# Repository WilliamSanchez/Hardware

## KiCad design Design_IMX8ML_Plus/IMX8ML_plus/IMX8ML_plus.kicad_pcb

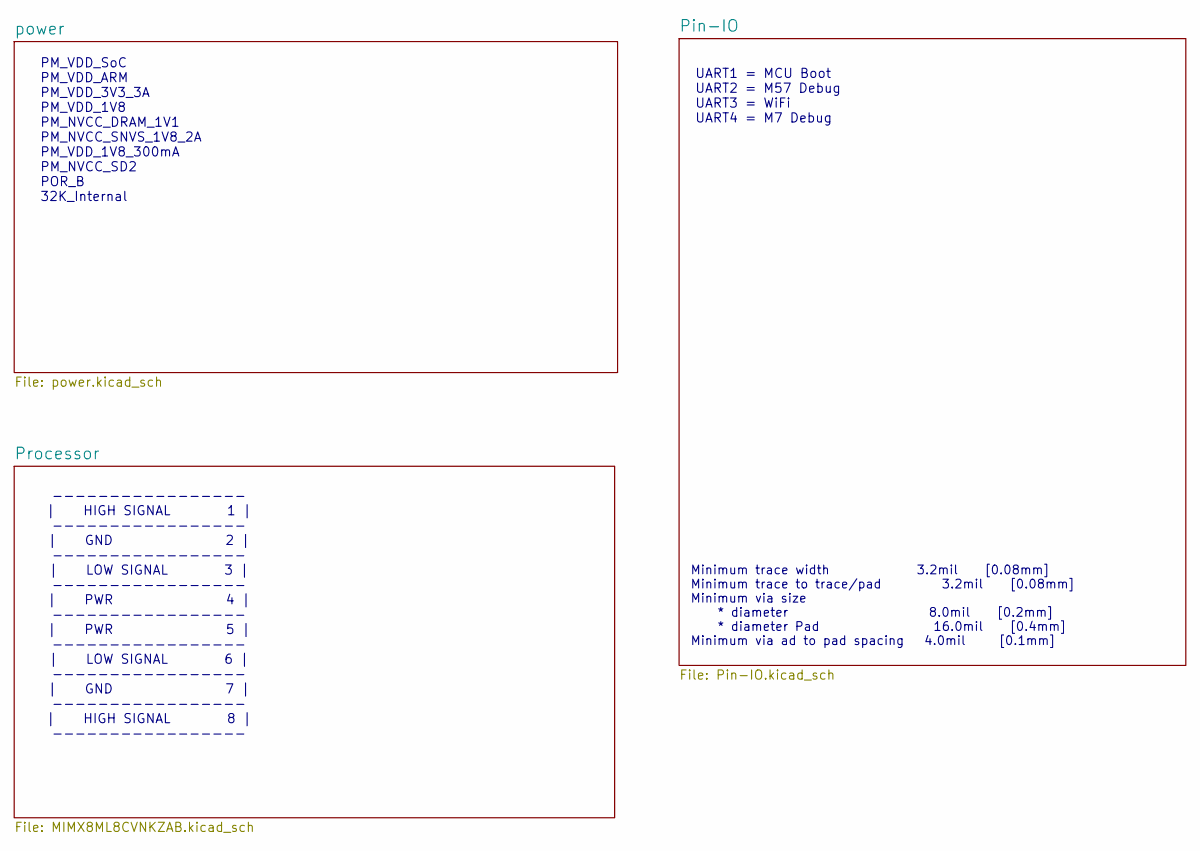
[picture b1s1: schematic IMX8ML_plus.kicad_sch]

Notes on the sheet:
----------------- | HIGH SIGNAL 1 | ----------------- | GND 2 | ----------------- | LOW SIGNAL 3 | ----------------- | PWR 4 | ----------------- | PWR 5 | ----------------- | LOW SIGNAL 6 | ----------------- | GND 7 | ----------------- | HIGH SIGNAL 8 | -----------------
UART1 = MCU Boot UART2 = M57 Debug UART3 = WiFi UART4 = M7 Debug
Minimum trace width 3.2mil [0.08mm] Minimum trace to trace/pad 3.2mil [0.08mm] Minimum via size * diameter 8.0mil [0.2mm] * diameter Pad 16.0mil [0.4mm] Minimum via ad to pad spacing 4.0mil [0.1mm]
PM_VDD_SoC PM_VDD_ARM PM_VDD_3V3_3A PM_VDD_1V8 PM_NVCC_DRAM_1V1 PM_NVCC_SNVS_1V8_2A PM_VDD_1V8_300mA PM_NVCC_SD2 POR_B 32K_Internal

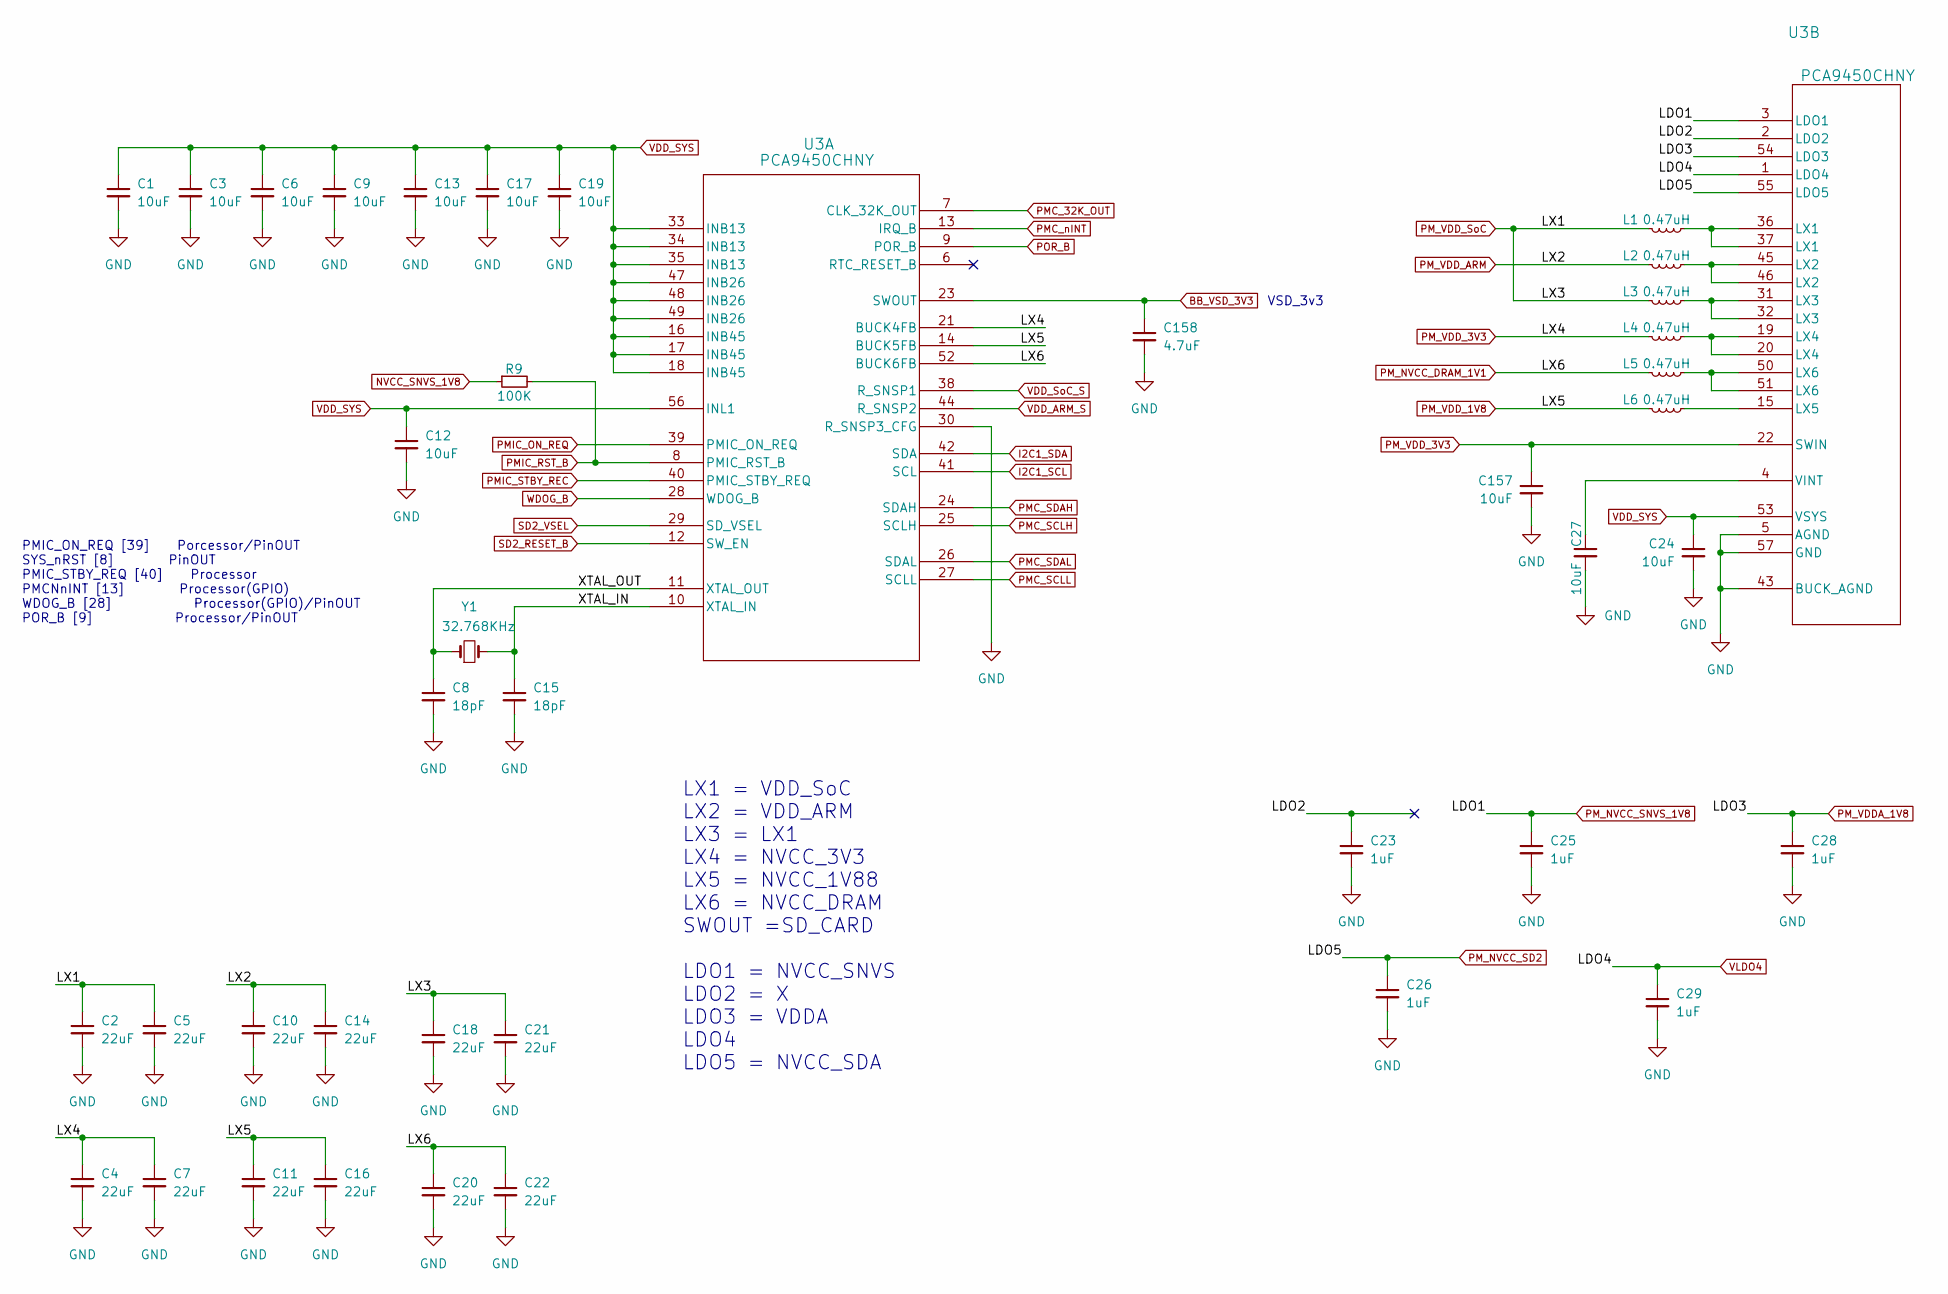
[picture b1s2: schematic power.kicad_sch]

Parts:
C1, C3, C6, C9, C12, C13, C17, C19, C157: 10uF; C_0603_1608Metric
C2, C4, C5, C7, C10, C11, C14, C16, C18, C20, C21, C22: 22uF; C_0603_1608Metric
C8, C15: 18pF; C_0201_0603Metric
C23, C25, C26, C28, C29: 1uF; C_0201_0603Metric
C24, C27: 10uF; C_0402_1005Metric
C158: 4.7uF; C_0402_1005Metric
L1, L2, L3, L4: 0.47uH; L_APV_ANR252012
L5, L6: 0.47uH; L_Cenker_CKCS201610
R9: 100K; R_0402_1005Metric
U3: PCA9450CHNY; HVQFN56_SOT949-6_NXP
Y1: 32.768KHz; Crystal_SMD_3215-2Pin_3.2x1.5mm

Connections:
/power/LDO2: C23.1, U3.2 (LDO2)
/power/XTAL_IN: C15.1, U3.10 (XTAL_IN), Y1.2
/power/XTAL_OUT: C8.1, U3.11 (XTAL_OUT), Y1.1
BB_VSD_3V3: C158.1, U3.23 (SWOUT)
GND: C1.2, C2.2, C3.2, C4.2, C5.2, C6.2, C7.2, C8.2, C9.2, C10.2, C11.2, C12.2, C13.2, C14.2, C15.2, C16.2, C17.2, C18.2, C19.2, C20.2, C21.2, C22.2, C23.2, C24.2, C25.2, C26.2, C27.2, C28.2, C29.2, C157.2, C158.2, U3.5 (AGND), U3.30 (R_SNSP3_CFG), U3.43 (BUCK_AGND), U3.57 (GND); also elsewhere on the board
I2C1_SCL: U3.41 (SCL); also elsewhere on the board
I2C1_SDA: U3.42 (SDA); also elsewhere on the board
NVCC_SD2: C26.1, U3.55 (LDO5); also elsewhere on the board
NVCC_SNVS_1V8: C25.1, R9.1, U3.3 (LDO1); also elsewhere on the board
unnamed: L1.1, U3.36 (LX1), U3.37 (LX1)
unnamed: L2.1, U3.45 (LX2), U3.46 (LX2)
unnamed: L3.1, U3.31 (LX3), U3.32 (LX3)
unnamed: L4.1, U3.19 (LX4), U3.20 (LX4)
unnamed: L5.1, U3.50 (LX6), U3.51 (LX6)
unnamed: L6.1, U3.15 (LX5)
unnamed: C27.1, U3.4 (VINT)
PMC_32K_OUT: U3.7 (CLK_32K_OUT)
PMC_SCLH: U3.25 (SCLH)
PMC_SCLL: U3.27 (SCLL)
PMC_SDAH: U3.24 (SDAH)
PMC_SDAL: U3.26 (SDAL)
PMC_nINT: U3.13 (IRQ_B); also elsewhere on the board
PMIC_ON_REQ: U3.39 (PMIC_ON_REQ); also elsewhere on the board
PMIC_RST_B: R9.2, U3.8 (PMIC_RST_B); also elsewhere on the board
PMIC_STBY_REC: U3.40 (PMIC_STBY_REQ); also elsewhere on the board
PM_NVCC_DRAM_1V1: C20.1, C22.1, L5.2, U3.52 (BUCK6FB)
PM_VDDA_1V8: C28.1, U3.54 (LDO3); also elsewhere on the board
PM_VDD_1V8: C11.1, C16.1, L6.2, U3.14 (BUCK5FB)
PM_VDD_3V3: C4.1, C7.1, C157.1, L4.2, U3.21 (BUCK4FB), U3.22 (SWIN); also elsewhere on the board
PM_VDD_ARM: C10.1, C14.1, L2.2, U3.44 (R_SNSP2); also elsewhere on the board
PM_VDD_SoC: C2.1, C5.1, C18.1, C21.1, L1.2, L3.2, U3.38 (R_SNSP1); also elsewhere on the board
POR_B: U3.9 (POR_B); also elsewhere on the board
SD2_RESET_B: U3.12 (SW_EN)
SD2_VSEL: U3.29 (SD_VSEL); also elsewhere on the board
VDD_SYS: C1.1, C3.1, C6.1, C9.1, C12.1, C13.1, C17.1, C19.1, C24.1, U3.16 (INB45), U3.17 (INB45), U3.18 (INB45), U3.33 (INB13), U3.34 (INB13), U3.35 (INB13), U3.47 (INB26), U3.48 (INB26), U3.49 (INB26), U3.53 (VSYS), U3.56 (INL1); also elsewhere on the board
VLDO4: C29.1, U3.1 (LDO4)
WDOG_B: U3.28 (WDOG_B); also elsewhere on the board

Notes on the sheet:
VSD_3v3
LX1 = VDD_SoC LX2 = VDD_ARM LX3 = LX1 LX4 = NVCC_3V3 LX5 = NVCC_1V88 LX6 = NVCC_DRAM SWOUT =SD_CARD LDO1 = NVCC_SNVS LDO2 = X LDO3 = VDDA LDO4 LDO5 = NVCC_SDA
PMIC_ON_REQ [39] Porcessor/PinOUT SYS_nRST [8] PinOUT PMIC_STBY_REQ [40] Processor PMCNnINT [13] Processor(GPIO) WDOG_B [28] Processor(GPIO)/PinOUT POR_B [9] Processor/PinOUT

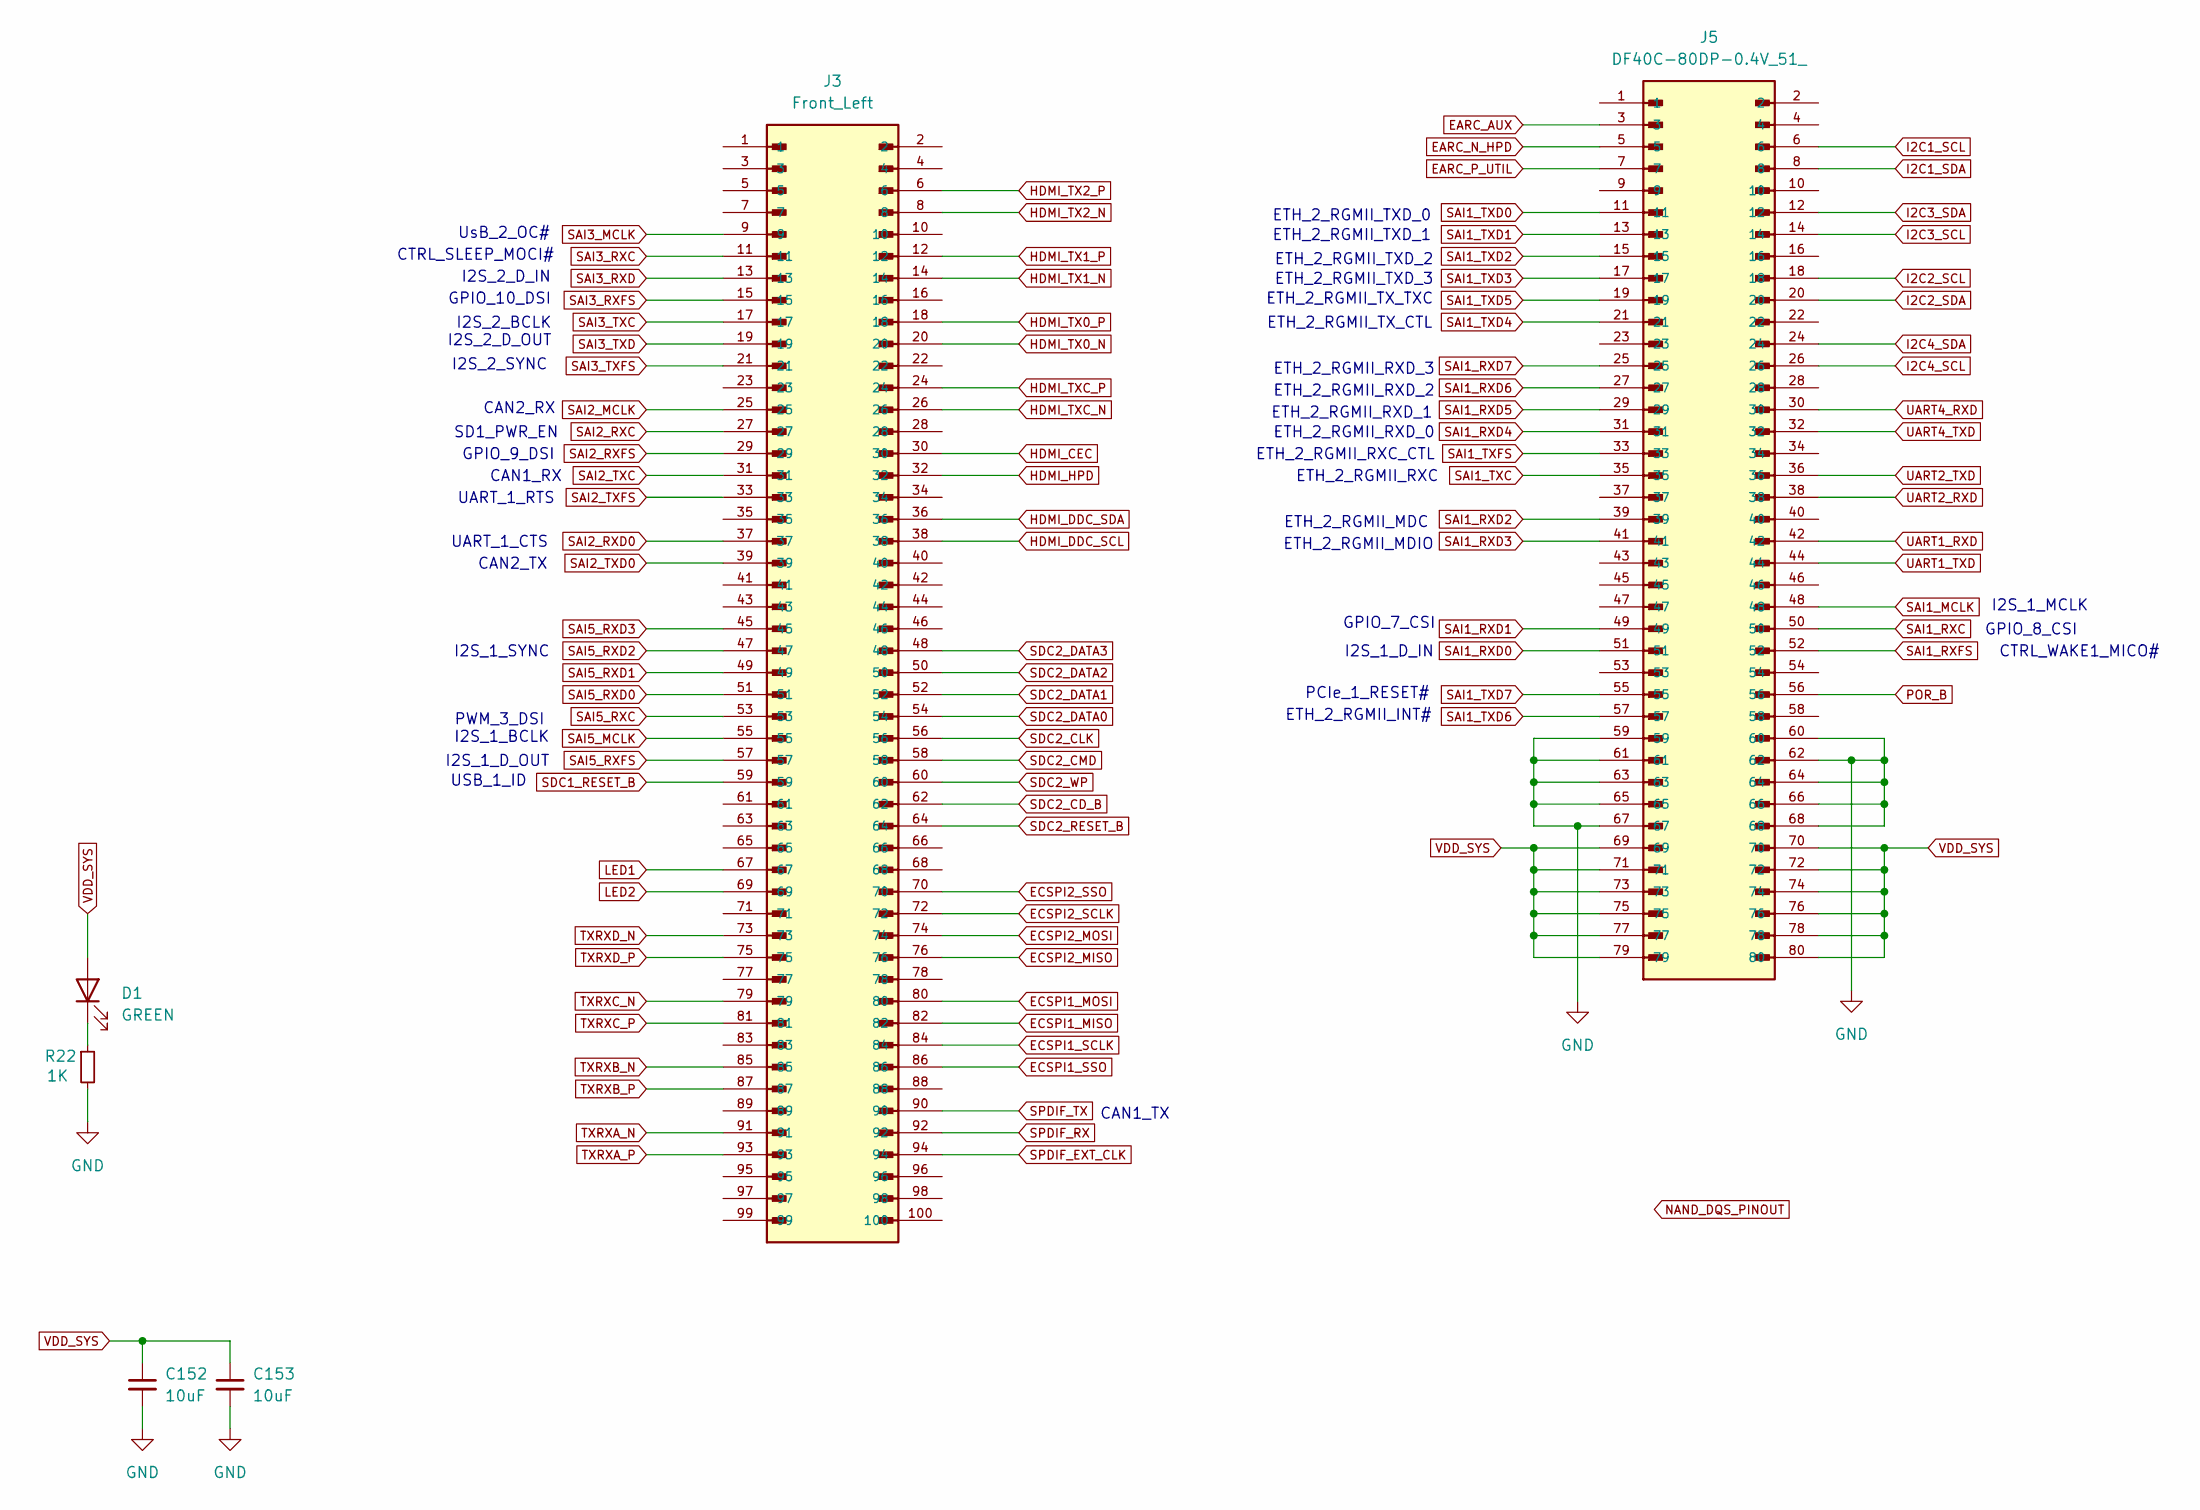
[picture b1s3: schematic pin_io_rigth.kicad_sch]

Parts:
C152, C153: 10uF; C_0603_1608Metric
D1: GREEN; LED_0603_1608Metric
J3: Front_Left; HIROSE_DF40C-100DS-0.4V_51_; PARTREV 8
J5: DF40C-80DP-0.4V_51_; HRS_DF40C-80DS-0.4V_51_
R22: 1K; R_0402_1005Metric

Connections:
EARC_AUX: J5.3; also elsewhere on the board
EARC_N_HPD: J5.5; also elsewhere on the board
EARC_P_UTIL: J5.7; also elsewhere on the board
ECSPI1_MISO: J3.82; also elsewhere on the board
ECSPI1_MOSI: J3.80; also elsewhere on the board
ECSPI1_SCLK: J3.84; also elsewhere on the board
ECSPI1_SSO: J3.86; also elsewhere on the board
ECSPI2_MISO: J3.76; also elsewhere on the board
ECSPI2_MOSI: J3.74; also elsewhere on the board
ECSPI2_SCLK: J3.72; also elsewhere on the board
ECSPI2_SSO: J3.70; also elsewhere on the board
GND: C152.2, C153.2, J5.59, J5.60, J5.61, J5.62, J5.63, J5.64, J5.65, J5.66, J5.67, J5.68, R22.2; also elsewhere on the board
HDMI_CEC: J3.30; also elsewhere on the board
HDMI_DDC_SCL: J3.38; also elsewhere on the board
HDMI_DDC_SDA: J3.36; also elsewhere on the board
HDMI_HPD: J3.32; also elsewhere on the board
HDMI_TX0_N: J3.20; also elsewhere on the board
HDMI_TX0_P: J3.18; also elsewhere on the board
HDMI_TX1_N: J3.14; also elsewhere on the board
HDMI_TX1_P: J3.12; also elsewhere on the board
HDMI_TX2_N: J3.8; also elsewhere on the board
HDMI_TX2_P: J3.6; also elsewhere on the board
HDMI_TXC_N: J3.26; also elsewhere on the board
HDMI_TXC_P: J3.24; also elsewhere on the board
I2C1_SCL: J5.6; also elsewhere on the board
I2C1_SDA: J5.8; also elsewhere on the board
I2C2_SCL: J5.18; also elsewhere on the board
I2C2_SDA: J5.20; also elsewhere on the board
I2C3_SCL: J5.14; also elsewhere on the board
I2C3_SDA: J5.12; also elsewhere on the board
I2C4_SCL: J5.26; also elsewhere on the board
I2C4_SDA: J5.24; also elsewhere on the board
LED1: J3.67; also elsewhere on the board
LED2: J3.69; also elsewhere on the board
unnamed: D1.1 (K), R22.1
POR_B: J5.56; also elsewhere on the board
SAI1_MCLK: J5.48; also elsewhere on the board
SAI1_RXC: J5.50; also elsewhere on the board
SAI1_RXD0: J5.51; also elsewhere on the board
SAI1_RXD1: J5.49; also elsewhere on the board
SAI1_RXD2: J5.39; also elsewhere on the board
SAI1_RXD3: J5.41; also elsewhere on the board
SAI1_RXD4: J5.31; also elsewhere on the board
SAI1_RXD5: J5.29; also elsewhere on the board
SAI1_RXD6: J5.27; also elsewhere on the board
SAI1_RXD7: J5.25; also elsewhere on the board
SAI1_RXFS: J5.52; also elsewhere on the board
SAI1_TXC: J5.35; also elsewhere on the board
SAI1_TXD0: J5.11; also elsewhere on the board
SAI1_TXD1: J5.13; also elsewhere on the board
SAI1_TXD2: J5.15; also elsewhere on the board
SAI1_TXD3: J5.17; also elsewhere on the board
SAI1_TXD4: J5.21; also elsewhere on the board
SAI1_TXD5: J5.19; also elsewhere on the board
SAI1_TXD6: J5.57; also elsewhere on the board
SAI1_TXD7: J5.55; also elsewhere on the board
SAI1_TXFS: J5.33; also elsewhere on the board
SAI2_MCLK: J3.25; also elsewhere on the board
SAI2_RXC: J3.27; also elsewhere on the board
SAI2_RXD0: J3.37; also elsewhere on the board
SAI2_RXFS: J3.29; also elsewhere on the board
SAI2_TXC: J3.31; also elsewhere on the board
SAI2_TXD0: J3.39; also elsewhere on the board
SAI2_TXFS: J3.33; also elsewhere on the board
SAI3_MCLK: J3.9; also elsewhere on the board
SAI3_RXC: J3.11; also elsewhere on the board
SAI3_RXD: J3.13; also elsewhere on the board
SAI3_RXFS: J3.15; also elsewhere on the board
SAI3_TXC: J3.17; also elsewhere on the board
SAI3_TXD: J3.19; also elsewhere on the board
SAI3_TXFS: J3.21; also elsewhere on the board
SAI5_MCLK: J3.55; also elsewhere on the board
SAI5_RXC: J3.53; also elsewhere on the board
SAI5_RXD0: J3.51; also elsewhere on the board
SAI5_RXD1: J3.49; also elsewhere on the board
SAI5_RXD2: J3.47; also elsewhere on the board
SAI5_RXD3: J3.45; also elsewhere on the board
SAI5_RXFS: J3.57; also elsewhere on the board
SDC1_RESET_B: J3.59
SDC2_CD_B: J3.62; also elsewhere on the board
SDC2_CLK: J3.56; also elsewhere on the board
SDC2_CMD: J3.58; also elsewhere on the board
SDC2_DATA0: J3.54; also elsewhere on the board
SDC2_DATA1: J3.52; also elsewhere on the board
SDC2_DATA2: J3.50; also elsewhere on the board
SDC2_DATA3: J3.48; also elsewhere on the board
SDC2_RESET_B: J3.64; also elsewhere on the board
SDC2_WP: J3.60; also elsewhere on the board
SPDIF_EXT_CLK: J3.94; also elsewhere on the board
SPDIF_RX: J3.92; also elsewhere on the board
SPDIF_TX: J3.90; also elsewhere on the board
TXRXA_N: J3.91; also elsewhere on the board
TXRXA_P: J3.93; also elsewhere on the board
TXRXB_N: J3.85; also elsewhere on the board
TXRXB_P: J3.87; also elsewhere on the board
TXRXC_N: J3.79; also elsewhere on the board
TXRXC_P: J3.81; also elsewhere on the board
TXRXD_N: J3.73; also elsewhere on the board
TXRXD_P: J3.75; also elsewhere on the board
UART1_RXD: J5.42; also elsewhere on the board
UART1_TXD: J5.44; also elsewhere on the board
UART2_RXD: J5.38; also elsewhere on the board
UART2_TXD: J5.36; also elsewhere on the board
UART4_RXD: J5.30; also elsewhere on the board
UART4_TXD: J5.32; also elsewhere on the board
VDD_SYS: C152.1, C153.1, D1.2 (A), J5.69, J5.70, J5.71, J5.72, J5.73, J5.74, J5.75, J5.76, J5.77, J5.78, J5.79, J5.80; also elsewhere on the board

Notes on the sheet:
PCIe_1_RESET#
I2S_1_MCLK
ETH_2_RGMII_MDC
CTRL_WAKE1_MICO#
CAN1_RX
I2S_2_BCLK
SD1_PWR_EN
I2S_1_D_IN
GPIO_9_DSI
I2S_1_SYNC
ETH_2_RGMII_RXD_3
UART_1_CTS
I2S_2_D_OUT
ETH_2_RGMII_TXD_2
CAN1_TX
ETH_2_RGMII_RXC_CTL
I2S_2_D_IN
ETH_2_RGMII_TXD_3
UART_1_RTS
ETH_2_RGMII_RXD_2
UsB_2_OC#
ETH_2_RGMII_RXD_0
CAN2_TX
I2S_1_D_OUT
I2S_1_BCLK
GPIO_8_CSI
CAN2_RX
ETH_2_RGMII_RXC
PWM_3_DSI
ETH_2_RGMII_TXD_0
GPIO_7_CSI
ETH_2_RGMII_TX_CTL
I2S_2_SYNC
ETH_2_RGMII_TXD_1
ETH_2_RGMII_INT#
USB_1_ID
CTRL_SLEEP_MOCI#
ETH_2_RGMII_TX_TXC
ETH_2_RGMII_MDIO
GPIO_10_DSI

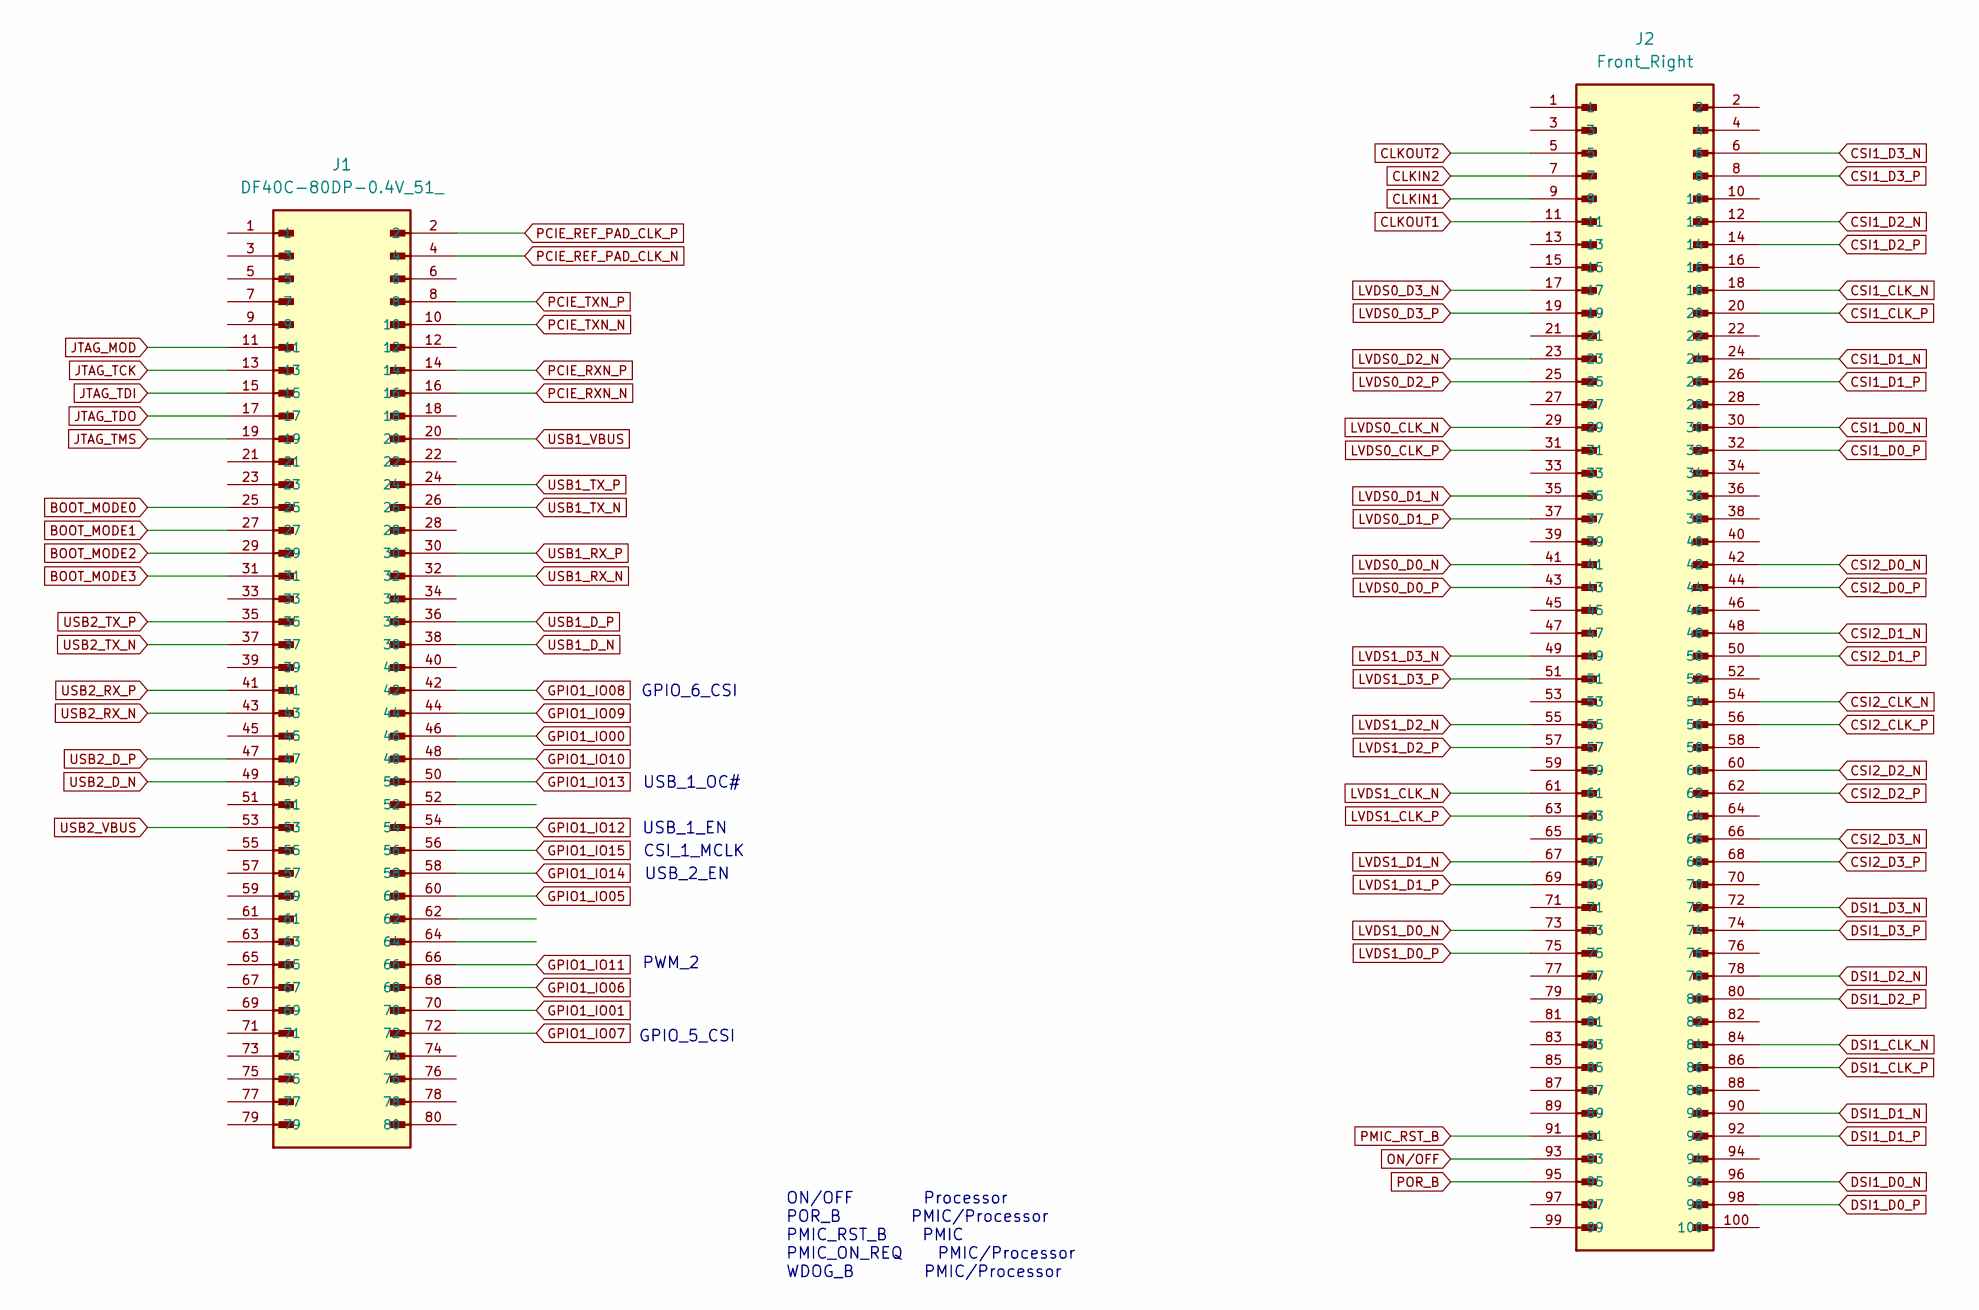
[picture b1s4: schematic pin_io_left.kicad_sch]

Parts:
J1: DF40C-80DP-0.4V_51_; HRS_DF40C-80DS-0.4V_51_
J2: Front_Right; HIROSE_DF40C-100DS-0.4V_51_; PARTREV 8

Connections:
BOOT_MODE0: J1.25; also elsewhere on the board
BOOT_MODE1: J1.27; also elsewhere on the board
BOOT_MODE2: J1.29; also elsewhere on the board
BOOT_MODE3: J1.31; also elsewhere on the board
CLKIN1: J2.9; also elsewhere on the board
CLKIN2: J2.7; also elsewhere on the board
CLKOUT1: J2.11; also elsewhere on the board
CLKOUT2: J2.5; also elsewhere on the board
CSI1_CLK_N: J2.18; also elsewhere on the board
CSI1_CLK_P: J2.20; also elsewhere on the board
CSI1_D0_N: J2.30; also elsewhere on the board
CSI1_D0_P: J2.32; also elsewhere on the board
CSI1_D1_N: J2.24; also elsewhere on the board
CSI1_D1_P: J2.26; also elsewhere on the board
CSI1_D2_N: J2.12; also elsewhere on the board
CSI1_D2_P: J2.14; also elsewhere on the board
CSI1_D3_N: J2.6; also elsewhere on the board
CSI1_D3_P: J2.8; also elsewhere on the board
CSI2_CLK_N: J2.54; also elsewhere on the board
CSI2_CLK_P: J2.56; also elsewhere on the board
CSI2_D0_N: J2.42; also elsewhere on the board
CSI2_D0_P: J2.44; also elsewhere on the board
CSI2_D1_N: J2.48; also elsewhere on the board
CSI2_D1_P: J2.50; also elsewhere on the board
CSI2_D2_N: J2.60; also elsewhere on the board
CSI2_D2_P: J2.62; also elsewhere on the board
CSI2_D3_N: J2.66; also elsewhere on the board
CSI2_D3_P: J2.68; also elsewhere on the board
DSI1_CLK_N: J2.84; also elsewhere on the board
DSI1_CLK_P: J2.86; also elsewhere on the board
DSI1_D0_N: J2.96; also elsewhere on the board
DSI1_D0_P: J2.98; also elsewhere on the board
DSI1_D1_N: J2.90; also elsewhere on the board
DSI1_D1_P: J2.92; also elsewhere on the board
DSI1_D2_N: J2.78; also elsewhere on the board
DSI1_D2_P: J2.80; also elsewhere on the board
DSI1_D3_N: J2.72; also elsewhere on the board
DSI1_D3_P: J2.74; also elsewhere on the board
GPIO1_IO00: J1.46; also elsewhere on the board
GPIO1_IO01: J1.70; also elsewhere on the board
GPIO1_IO05: J1.60; also elsewhere on the board
GPIO1_IO06: J1.68; also elsewhere on the board
GPIO1_IO07: J1.72; also elsewhere on the board
GPIO1_IO08: J1.42; also elsewhere on the board
GPIO1_IO09: J1.44; also elsewhere on the board
GPIO1_IO10: J1.48; also elsewhere on the board
GPIO1_IO11: J1.66; also elsewhere on the board
GPIO1_IO12: J1.54; also elsewhere on the board
GPIO1_IO13: J1.50; also elsewhere on the board
GPIO1_IO14: J1.58; also elsewhere on the board
GPIO1_IO15: J1.56; also elsewhere on the board
JTAG_MOD: J1.11; also elsewhere on the board
JTAG_TCK: J1.13; also elsewhere on the board
JTAG_TDI: J1.15; also elsewhere on the board
JTAG_TDO: J1.17; also elsewhere on the board
JTAG_TMS: J1.19; also elsewhere on the board
LVDS0_CLK_N: J2.29; also elsewhere on the board
LVDS0_CLK_P: J2.31; also elsewhere on the board
LVDS0_D0_N: J2.41; also elsewhere on the board
LVDS0_D0_P: J2.43; also elsewhere on the board
LVDS0_D1_N: J2.35; also elsewhere on the board
LVDS0_D1_P: J2.37; also elsewhere on the board
LVDS0_D2_N: J2.23; also elsewhere on the board
LVDS0_D2_P: J2.25; also elsewhere on the board
LVDS0_D3_N: J2.17; also elsewhere on the board
LVDS0_D3_P: J2.19; also elsewhere on the board
LVDS1_CLK_N: J2.61; also elsewhere on the board
LVDS1_CLK_P: J2.63; also elsewhere on the board
LVDS1_D0_N: J2.73; also elsewhere on the board
LVDS1_D0_P: J2.75; also elsewhere on the board
LVDS1_D1_N: J2.67; also elsewhere on the board
LVDS1_D1_P: J2.69; also elsewhere on the board
LVDS1_D2_N: J2.55; also elsewhere on the board
LVDS1_D2_P: J2.57; also elsewhere on the board
LVDS1_D3_N: J2.49; also elsewhere on the board
LVDS1_D3_P: J2.51; also elsewhere on the board
ON/OFF: J2.93; also elsewhere on the board
PCIE_REF_PAD_CLK_N: J1.4; also elsewhere on the board
PCIE_REF_PAD_CLK_P: J1.2; also elsewhere on the board
PCIE_RXN_N: J1.16; also elsewhere on the board
PCIE_RXN_P: J1.14; also elsewhere on the board
PCIE_TXN_N: J1.10; also elsewhere on the board
PCIE_TXN_P: J1.8; also elsewhere on the board
PMIC_RST_B: J2.91; also elsewhere on the board
POR_B: J2.95; also elsewhere on the board
USB1_D_N: J1.38; also elsewhere on the board
USB1_D_P: J1.36; also elsewhere on the board
USB1_RX_N: J1.32; also elsewhere on the board
USB1_RX_P: J1.30; also elsewhere on the board
USB1_TX_N: J1.26; also elsewhere on the board
USB1_TX_P: J1.24; also elsewhere on the board
USB1_VBUS: J1.20; also elsewhere on the board
USB2_D_N: J1.49; also elsewhere on the board
USB2_D_P: J1.47; also elsewhere on the board
USB2_RX_N: J1.43; also elsewhere on the board
USB2_RX_P: J1.41; also elsewhere on the board
USB2_TX_N: J1.37; also elsewhere on the board
USB2_TX_P: J1.35; also elsewhere on the board
USB2_VBUS: J1.53; also elsewhere on the board

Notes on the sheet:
PWM_2
CSI_1_MCLK
ON/OFF Processor POR_B PMIC/Processor PMIC_RST_B PMIC PMIC_ON_REQ PMIC/Processor WDOG_B PMIC/Processor
USB_2_EN
GPIO_6_CSI
GPIO_5_CSI
USB_1_OC#
USB_1_EN

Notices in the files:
parts and their libraries:
Copyright 2016 Accelerated Designs. All rights reserved.
Copyright 2021 Accelerated Designs. All rights reserved.
